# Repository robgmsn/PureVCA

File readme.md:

DESIGN STATUS: Production

VCA Updated to V2.31 14/4/21

Library updated to include 3D models.
Traces rerouted.
Weird shorted cap removed. WTF?
Values tweaked for better CV response.

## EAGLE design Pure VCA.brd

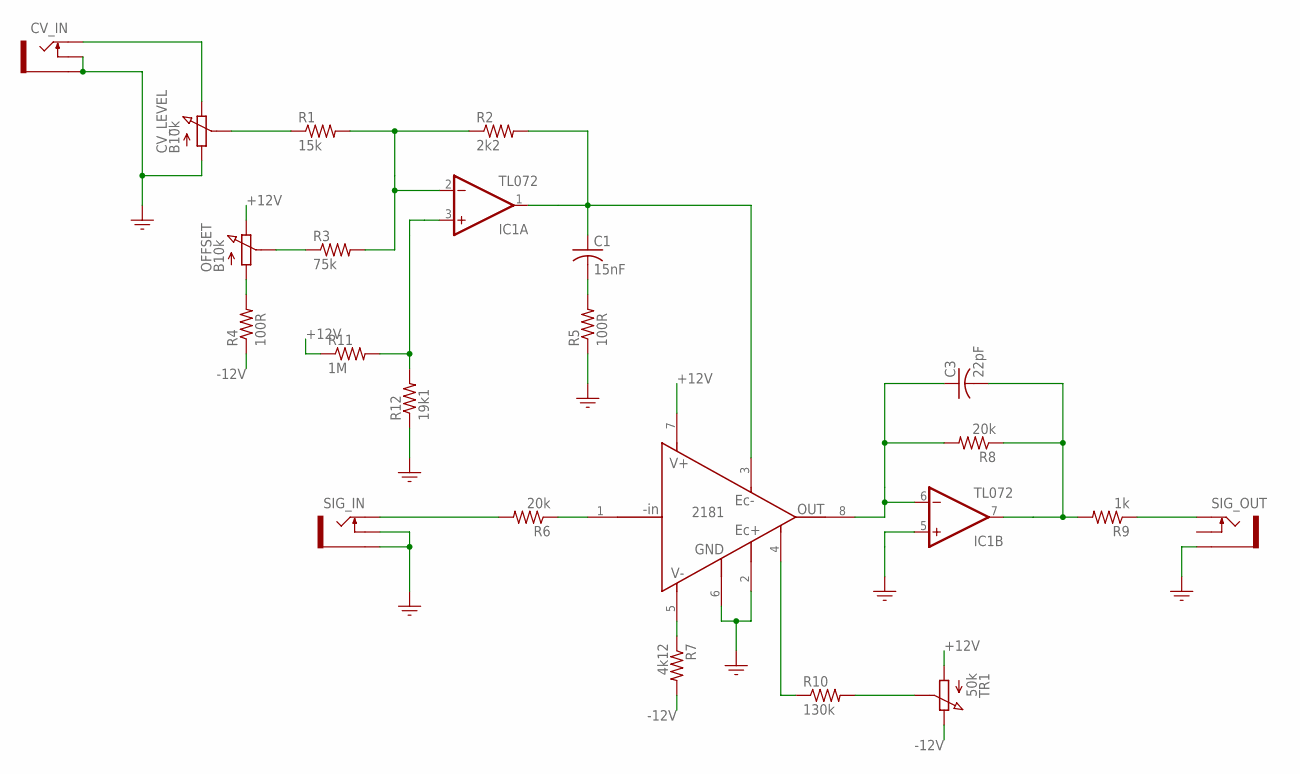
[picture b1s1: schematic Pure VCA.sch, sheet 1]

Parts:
C1: 15nF; C0805
C3: 22pF; C0805
CV_IN: PJ301M-12
CV_LEVEL: B10k; POT_9MM_GREEN_KNOB
IC1: TL072; SO08
IC2: THAT2181; SOIC--8
OFFSET: B10k; POT_9MM_BLUE_KNOB
R1: 15k; R0805
R2: 2k2; R0805
R3: 75k; R0805
R4, R5: 100R; R0805
R6, R8: 20k; R0805
R7: 4k12; R0805
R9: 1k; R0805
R10: 130k; R0805
R11: 1M; R0805
R12: 19k1; R0805
SIG_IN: PJ301M-12
SIG_OUT: PJ301M-12
TR1: 50k; TRIMMER_TH

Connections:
+12V: IC2.7 (V+), OFFSET.P$3 (3), R11.1, TR1.1; also elsewhere on the board
-12V: R4.1, R7.2, TR1.3; also elsewhere on the board
GND: CV_IN.GND (SLEEVE), CV_IN.NORM (SWITCH), CV_LEVEL.P$1 (1), IC1.5 (+IN), IC2.2 (EC+), IC2.6 (GND), R5.1, R12.1, SIG_IN.GND (SLEEVE), SIG_IN.NORM (SWITCH), SIG_OUT.GND (SLEEVE); also elsewhere on the board
unnamed: CV_IN.TIP, CV_LEVEL.P$3 (3)
unnamed: IC1.2 (-IN), R1.2, R2.1, R3.2
unnamed: CV_LEVEL.P$2 (2), R1.1
unnamed: OFFSET.P$1 (1), R4.2
unnamed: C1.1, IC1.1 (OUT), IC2.3 (EC-), R2.2
unnamed: OFFSET.P$2 (2), R3.1
unnamed: C1.2, R5.2
unnamed: R9.1, SIG_OUT.TIP
unnamed: IC2.1 (-IN), R6.1
unnamed: R6.2, SIG_IN.TIP
unnamed: IC2.5 (V-), R7.1
unnamed: IC1.3 (+IN), R11.2, R12.2
unnamed: C3.1, IC1.6 (-IN), IC2.8 (OUT), R8.2
unnamed: C3.2, IC1.7 (OUT), R8.1, R9.2
unnamed: IC2.4 (SYM), R10.1
unnamed: R10.2, TR1.2

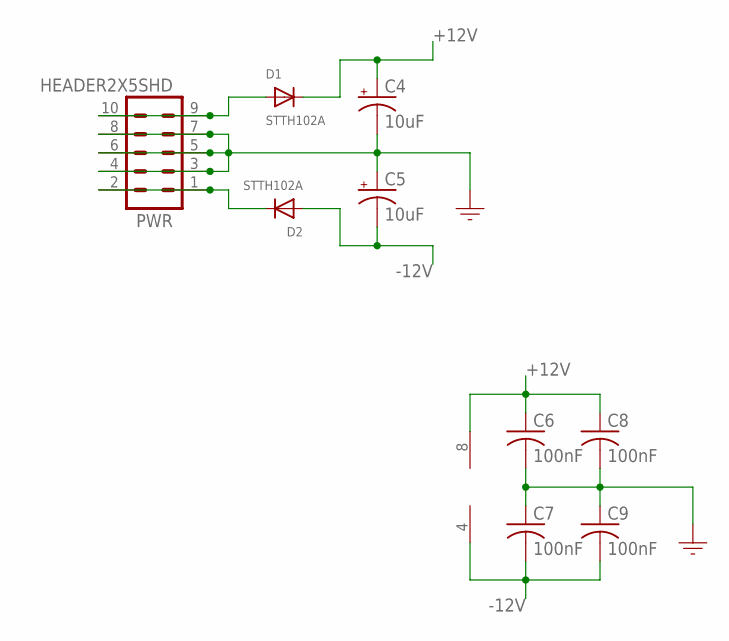
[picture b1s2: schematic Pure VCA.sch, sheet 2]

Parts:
C4, C5: 10uF; 153CLV-0505
C6, C7, C8, C9: 100nF; C0805
D1, D2: STTH102A; SMADIODE
IC1: TL072; SO08
PWR: HEADER2X5SHD; 2X5-SHROUDED

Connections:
+12V: C4.+, C6.1, C8.1, D1.C, IC1.8 (V+); also elsewhere on the board
-12V: C5.-, C7.2, C9.2, D2.A, IC1.4 (V-); also elsewhere on the board
GND: C4.-, C5.+, C6.2, C7.1, C8.2, C9.1, PWR.3, PWR.4, PWR.5, PWR.6, PWR.7, PWR.8; also elsewhere on the board
unnamed: D1.A, PWR.9, PWR.10
unnamed: D2.C, PWR.1, PWR.2

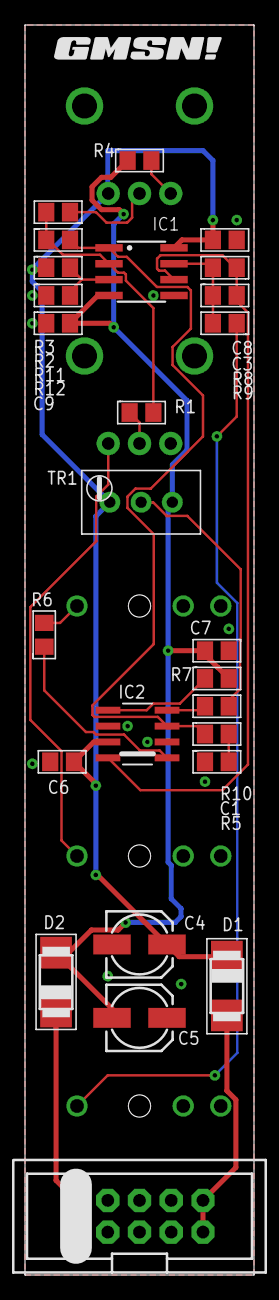
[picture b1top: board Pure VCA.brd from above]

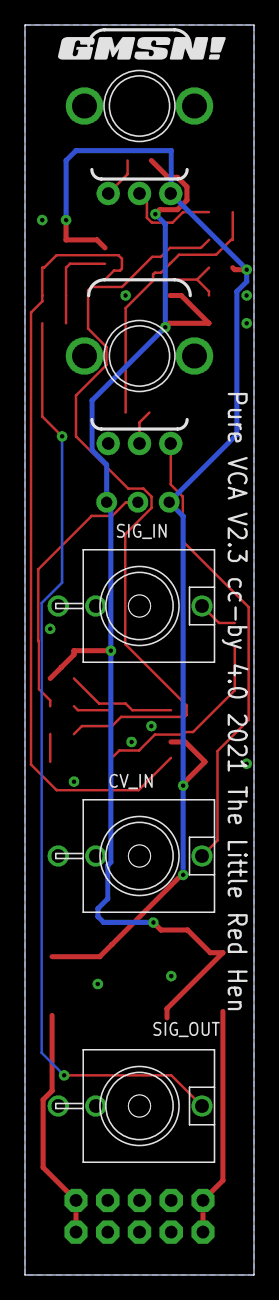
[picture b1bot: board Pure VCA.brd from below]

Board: 2 copper layers, 18.3 x 100.0 mm, 33 parts (6 on the bottom side), 21 nets.

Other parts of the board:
U$1, U$2: GMSN!_LOGO

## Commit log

2021-04-16 VCA 2.1
    Converted to SMD and changed from RS Design Spark to Eagle
2021-04-16 VCA 2.2
2021-04-16 VCA 2.3
    VCA Updated to V2.3 14/4/21
    Library updated to include 3D models.
    Traces rerouted.
    Weird shorted cap removed. WTF?
2021-04-16 Backlink to CADLAB.io has been added.
2021-04-27 VCA 2.31
    VCA Updated to V2.31 14/4/21
    Library updated to include 3D models.
    Traces rerouted.
    Weird shorted cap removed. WTF?
    Values tweaked for better CV response.

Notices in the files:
Pure VCA.brd:
Pure VCA V2.3 cc-by 4.0 2021 The Little Red Hen
